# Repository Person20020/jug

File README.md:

# Jug

A 6x3 column staggered split keyboard with a large thumb cluster.

The jug is a 6x3 column staggered split keyboard with 46 keys. It has a 5 key thumb cluster extending out to reduce reaching back with your thumb. It uses USB C for interconnect and includes two indicator leds per side for caps/num lock and layer (eg. Colemak vs QWERTY).

The PCB supports both hotswap sockets and directly soldering the switches. It is fully reversible and uses soldered jumpers for the MCU, a RP2040 Zero.

All components are placed so that the case sides are exact mirrors.

## Parts

### Electronics

| Part                                     | Count | Price ($)                    | Link                                                                                                                                               |
| ---------------------------------------- | ----- | ---------------------------- | -------------------------------------------------------------------------------------------------------------------------------------------------- |
| RP2040 Zero                              | 2     | ~4 each                      |                                                                                                                                                    |
| MX Switches                              | 46    | ~20-30                       |                                                                                                                                                    |
| Hotswap Sockets (optional)               | 46    | ~10 for 70 on AliExpress     |                                                                                                                                                    |
| 1n4148 Diodes                            | 46    | ~2 for 100 on AliExpress     |                                                                                                                                                    |
| USB C Ports                              | 2     | 0.40 (5 min order on lcsc)   | [https://lcsc.com/product-detail/image/GT-USB-7010ASV_C2988369.html](https://lcsc.com/product-detail/image/GT-USB-7010ASV_C2988369.html)           |
| 1206 SMD LEDs (I used red and blue leds) | 4     | 0.42 (100 min order on lcsc) | [blue](https://lcsc.com/product-detail/image/XL-3216UBC_C965827.html) or [red](https://lcsc.com/product-detail/image/XL-1608SURC-06_C965799.html)  |
| 1206 35.7 ohm SMD Resistors              | 4     | 0.18                         | [https://lcsc.com/product-detail/image/RC1206FR-0735R7L_C488810.html](https://lcsc.com/product-detail/image/RC1206FR-0735R7L_C488810.html)         |
| 1206 5.1k ohm SMD Resistors              | 2     | 0.22                         | [https://lcsc.com/product-detail/image/FRC1206J512-TS_C2907509.html](https://lcsc.com/product-detail/image/FRC1206J512-TS_C2907509.html)           |

### Other

| Part                                | Count |
| ----------------------------------- | ----- |
| 1u Keycaps                          | 42    |
| 1.5u Keycaps                        | 4     |
| 8mm m2 Standoffs                    | 14    |
| m2 x 4mm Screws                     | 28    |
| m2 x 12mm Screws                    | 4     |
| m3 x 12mm Screws                    | 12    |
| m3 Heat Set Inserts (5mm OD, 4mm L) | 12    |

I used socket head screws with hex drives. For the m2 screws screwed into the standoffs on the top (from the plate side, there are 14 of these) you will need to have screws that have a low enough head so that they don't hit the keycaps. I used [these](https://www.aliexpress.us/item/3256804883804669.html).

If you don't want to buy keycaps you can also print some like the [ScottoCaps](https://github.com/joe-scotto/scottokeebs/tree/main/Extras/ScottoCaps).

## Case

The case can be printed in its provided orientation, with the bottom to the build plate. The screw holes have sacrificial bridges in them to allow it to print cleanly. After printing, use a knife to cut through them. Other than that there should be no cleanup necessary.

## Firmware

I made both plain QMK and a Vial version of the firmware. They both have Colemak for the base layer with QWERTY as a second layer. You can set QWERTY as the base layer by moving the ` = 0` to `_QWERTY` from `_COLEMAK` in the keymap.c file, changing this:

```
enum layer_number {
    _COLEMAK = 0,
    _QWERTY,
    _LOWER,
    _RAISE,
    _ADJUST
};
```

to this:

```
enum layer_number {
    _COLEMAK,
    _QWERTY = 0,
    _LOWER,
    _RAISE,
    _ADJUST
};
```

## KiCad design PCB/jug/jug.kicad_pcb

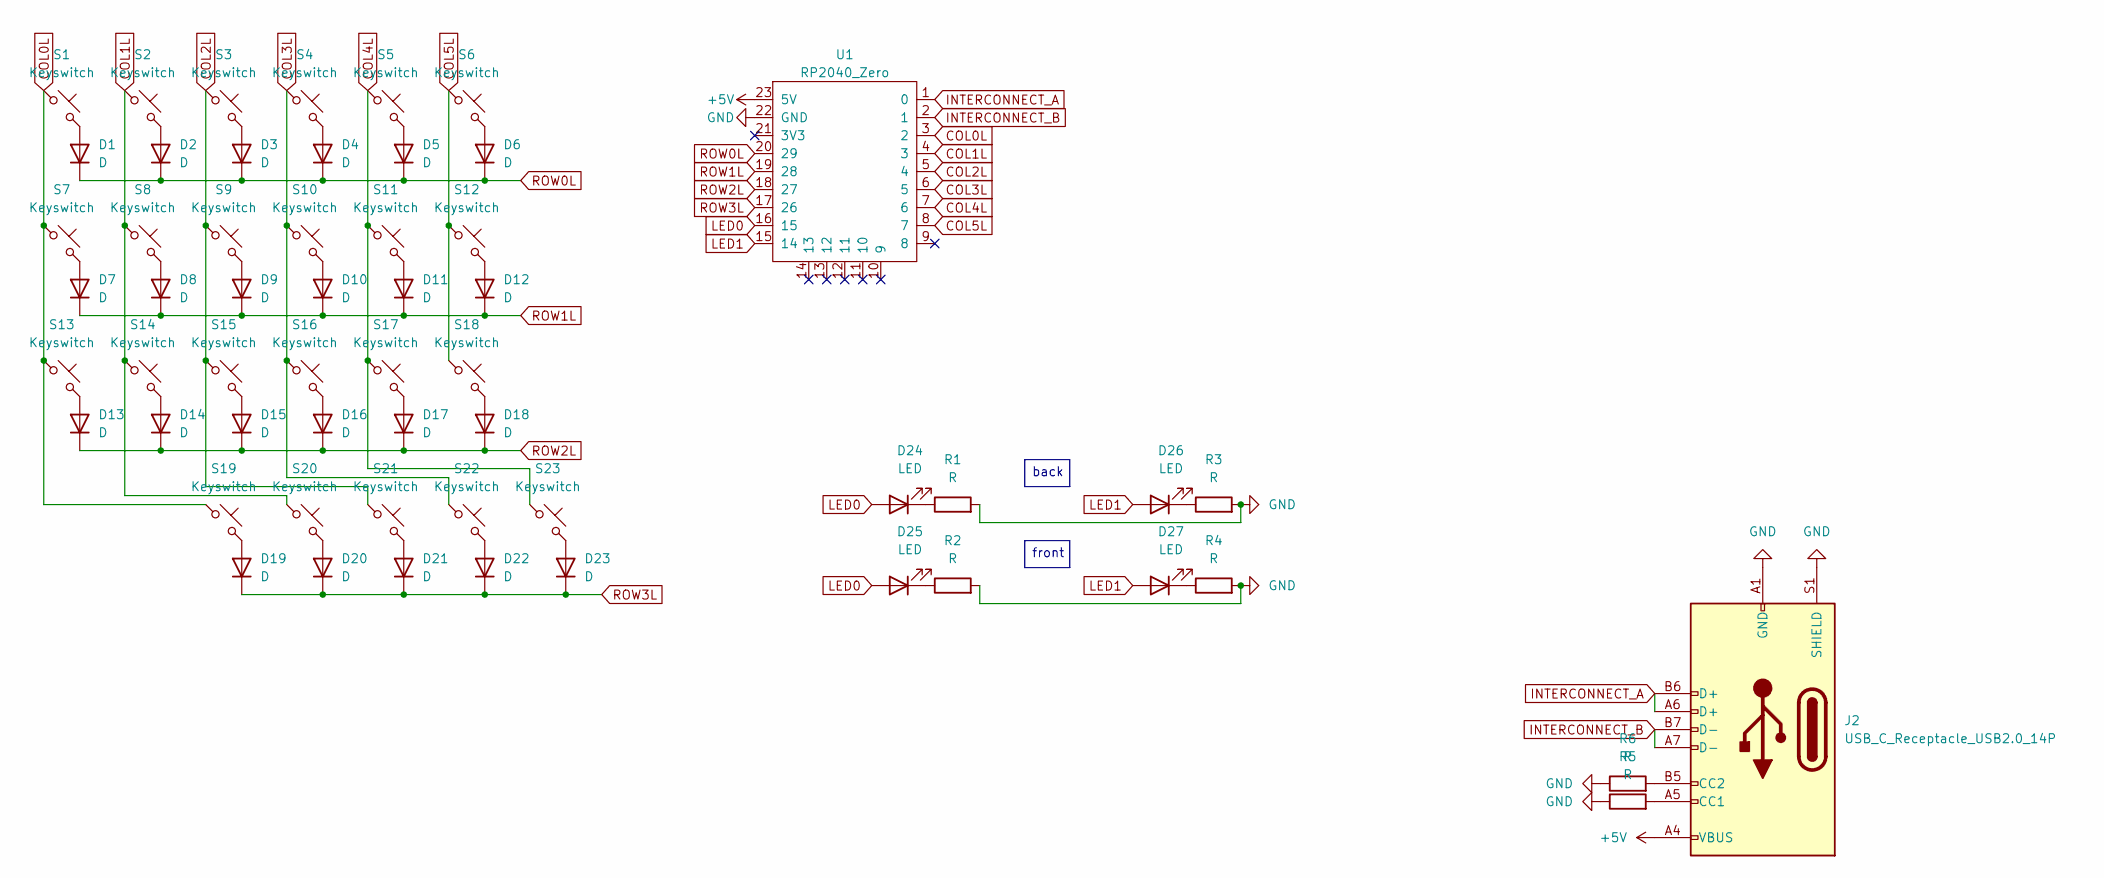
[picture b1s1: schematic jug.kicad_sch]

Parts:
D1, D2, D3, D4, D5, D6, D7, D8, D9, D10, D11, D12, D13, D14, D15, D16, D17, D18, D19, D20, D21, D22, D23: D; Double_Sided_Diode_DO-35
D24, D25, D26, D27: LED; LED_1206_3216Metric_Pad1.42x1.75mm_HandSolder
J2: USB_C_Receptacle_USB2.0_14P; USB_C_Receptacle_G-Switch_GT-USB-7010ASV_Double-Sided
R1, R2, R3, R4, R5, R6: R; R_1206_3216Metric_Pad1.30x1.75mm_HandSolder
S1, S2, S3, S4, S5, S6, S7, S8, S9, S10, S11, S12, S13, S14, S15, S16, S17, S18, S19, S20, S21: Keyswitch; Hotswap_MX_Plated_1.00u_Reversible
S22, S23: Keyswitch; Hotswap_MX_Plated_1.50u_90deg_Reversible
U1: RP2040_Zero; RP2040_Zero_Reversible

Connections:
+5V: J2.A4 (VBUS), J2.A9 (VBUS), J2.B4 (VBUS), J2.B9 (VBUS), U1.23 (5V)
COL0L: S1.1, S7.1, S13.1, S19.1, U1.3 (2)
COL1L: S2.1, S8.1, S14.1, S20.1, U1.4 (3)
COL2L: S3.1, S9.1, S15.1, S21.1, U1.5 (4)
COL3L: S4.1, S10.1, S16.1, S22.1, U1.6 (5)
COL4L: S5.1, S11.1, S17.1, S23.1, U1.7 (6)
COL5L: S6.1, S12.1, S18.1, U1.8 (7)
GND: J2.A1 (GND), J2.A12 (GND), J2.B1 (GND), J2.B12 (GND), J2.S1 (SHIELD), R1.2, R2.2, R3.2, R4.2, R5.1, R6.1, U1.22 (GND)
INTERCONNECT_A: J2.A6 (D+), J2.B6 (D+), U1.1 (0)
INTERCONNECT_B: J2.A7 (D-), J2.B7 (D-), U1.2 (1)
LED0: D24.2 (A), D25.2 (A), U1.16 (15)
LED1: D26.2 (A), D27.2 (A), U1.15 (14)
unnamed: D1.2 (A), S1.2
unnamed: D2.2 (A), S2.2
unnamed: D3.2 (A), S3.2
unnamed: D4.2 (A), S4.2
unnamed: D5.2 (A), S5.2
unnamed: D6.2 (A), S6.2
unnamed: D7.2 (A), S7.2
unnamed: D8.2 (A), S8.2
unnamed: D9.2 (A), S9.2
unnamed: D10.2 (A), S10.2
unnamed: D11.2 (A), S11.2
unnamed: D12.2 (A), S12.2
unnamed: D13.2 (A), S13.2
unnamed: D14.2 (A), S14.2
unnamed: D15.2 (A), S15.2
unnamed: D16.2 (A), S16.2
unnamed: D17.2 (A), S17.2
unnamed: D18.2 (A), S18.2
unnamed: D19.2 (A), S19.2
unnamed: D20.2 (A), S20.2
unnamed: D21.2 (A), S21.2
unnamed: D22.2 (A), S22.2
unnamed: D23.2 (A), S23.2
unnamed: D24.1 (K), R1.1
unnamed: D25.1 (K), R2.1
unnamed: D26.1 (K), R3.1
unnamed: D27.1 (K), R4.1
unnamed: J2.A5 (CC1), R5.2
unnamed: J2.B5 (CC2), R6.2
ROW0L: D1.1 (K), D2.1 (K), D3.1 (K), D4.1 (K), D5.1 (K), D6.1 (K), U1.20 (29)
ROW1L: D7.1 (K), D8.1 (K), D9.1 (K), D10.1 (K), D11.1 (K), D12.1 (K), U1.19 (28)
ROW2L: D13.1 (K), D14.1 (K), D15.1 (K), D16.1 (K), D17.1 (K), D18.1 (K), U1.18 (27)
ROW3L: D19.1 (K), D20.1 (K), D21.1 (K), D22.1 (K), D23.1 (K), U1.17 (26)

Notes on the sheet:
back
front

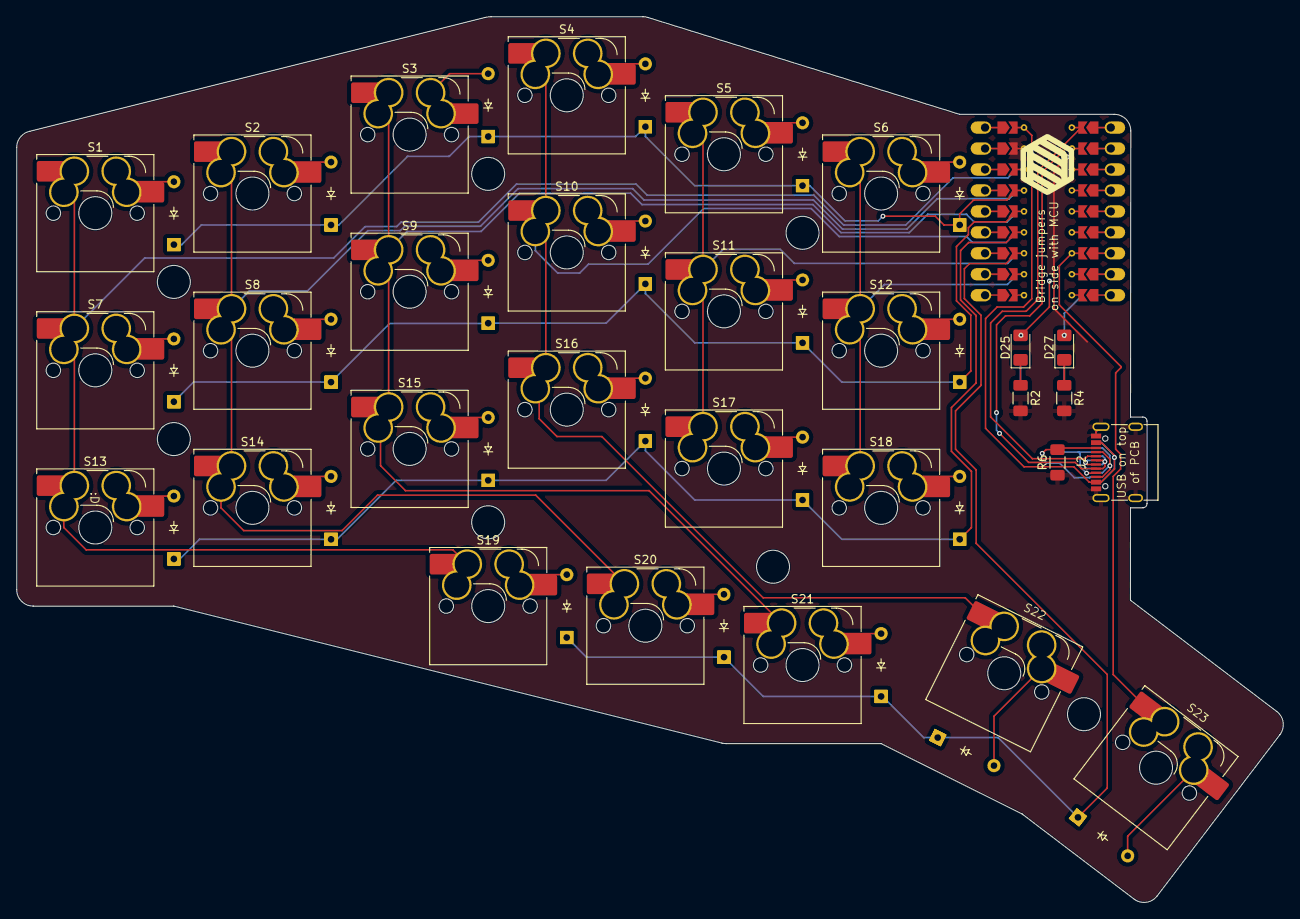
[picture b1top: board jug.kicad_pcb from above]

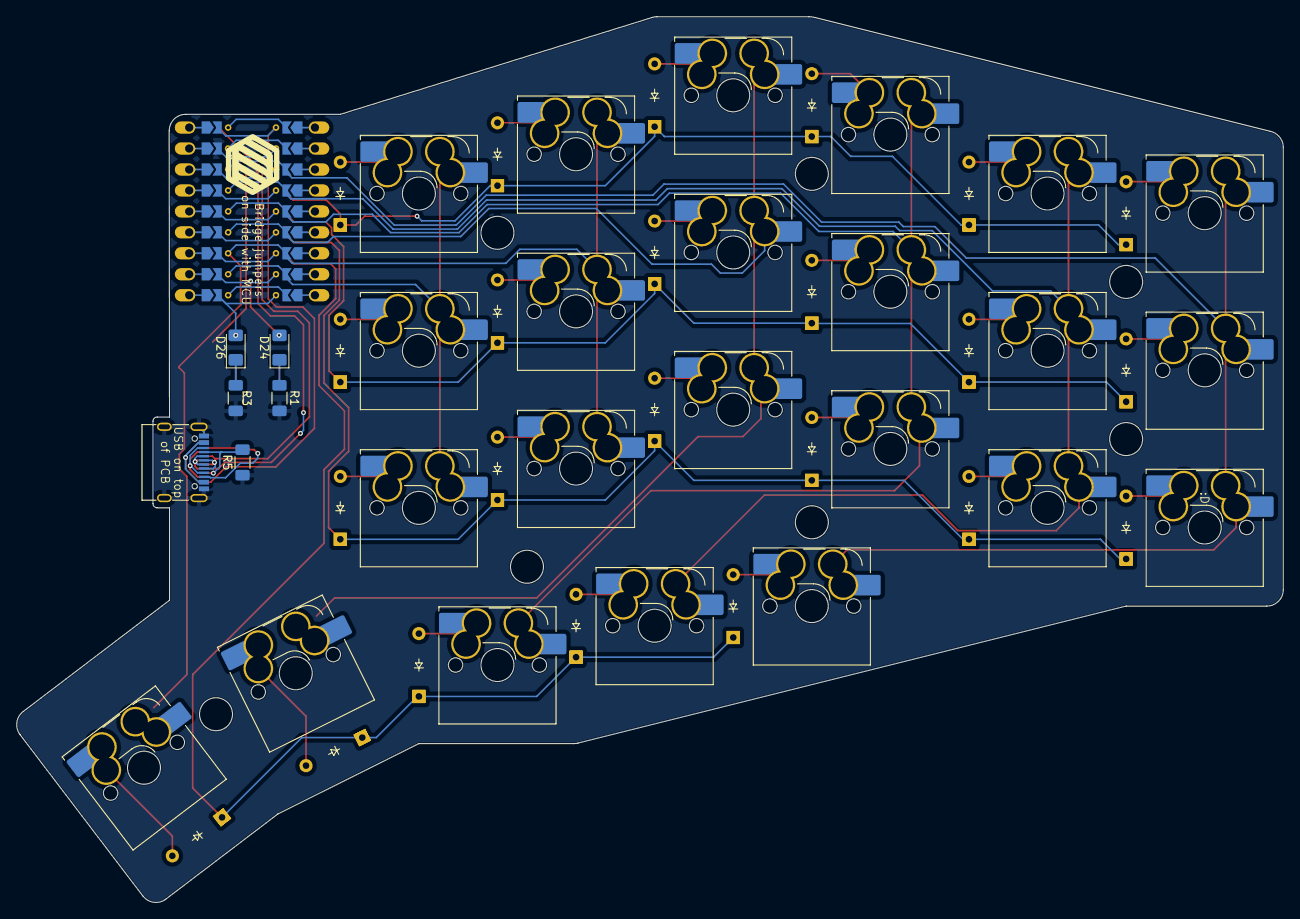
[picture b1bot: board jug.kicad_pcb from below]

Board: 2 copper layers, 153.5 x 107.4 mm, 58 parts (5 on the bottom side), 45 nets.

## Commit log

2025-06-29 first version of pcb. only left side routed. uses non reversible footprint for switches.
2025-07-02 finished pcb with RP2040 Pro Micro
2025-07-02 added journal
2025-07-02 changed mcu to rp2040 zero with reversible footprint
2025-07-03 finished pcb
2025-07-03 changed usb a to c
2025-07-07 everything finished
2025-07-07 added images of pcb design to readme
2025-07-27 Update README.md-- added image
2025-09-08 add logo to readme
2025-09-22 journal for build process
2026-03-12 add cdn rescue urls
2026-03-23 add journal.person20020.dev fontmatter data
2026-03-23 Fix old cdn links in readme
2026-03-23 Add image to journal
2026-03-24 Fix broken cdn links again
2026-03-24 Replace slack image link with cdn image link
